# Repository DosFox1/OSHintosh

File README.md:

# OSHintosh
OSHintosh - an open source hardware Diskless 68000 Macintosh with a Bootable ROM Disk, using absolutely no hardware from Apple!

# DISCLAIMER
The initial VDEV1 board required a large amount of bodges to become operational, these are as follows:

1) Added missing track between pin 1 of the 74ls161s, and pin 8 of the 74ls04 inverter
2) 1x missing 47R resistor TSEN2 from pin 11 of the TSG and ASG to ground
3) 4x missing 2k2 pull up resistors on address lines A9, A10, A11, A12
4) 2x missing 3k3 pull up resistors on !AS and !VIAIRQ
5) pin 4 of IC43 should be connected to -12v, not GND
6) pin 12 of IC18 should be connected to track VA11, not track VA12
7) pin 8 of IC43 should be connected to +12v, not 5V
8) errors on silkscreen for R68, R69, R70 and R71 (Schematic and BOM correct, silkscreen incorrect)
9) errors on silkscreen for R40 and R43 (Schematic and BOM correct, silkscreen incorrect)

VDEV2 has been completed and uploaded. This version should fix all problems with the VDEV1 board, but has not been tested. 

# Renders of the VDEV2 Board

# So, what is it?
In a nutshell, the OSHintosh is a Macintosh 512Ke Logic Board - but with the exception that it boots from a disk baked into the ROM, power it provided by an ATX power supply, there is an integrated Pico Scan Converter, as well as a SCHWIM to replace the IWM.
The ROM disk is based off the excellent original (ROMinator)[https://www.bigmessowires.com/mac-rom-inator/], and the OSHintosh also has the option to access further files from a LocalTalk server. 

There is no SCSI, No Floppy Drive or any other Mass Storage - it is effectively a Diskless Workstation!
It could be considered to be the spiritual sucessor to the Macintosh XO (also known as the Macintosh Classic!)

The board has also been designed in only two layers, which reduces the cost of the board even further.
JLCPCB suggest that five boards will cost £30 - so only £6 per board. Your mileage may vary. 
41256 RAM was chosen, as it at least avoids the issue of trying to source 30 pin RAM sockets - which are weirdly expensive now. 
It also makes the entire thing a DIP THT Macintosh!

This makes it the first Macintosh designed on a two layer PCB since the "SCC Word Wide" Prototype from 1982!
The board is more or less ATX shaped, but I didn't place the mounting holes to be ATX compliant. Sorry!

This is intended to fit somewhere between the excellent ITX Plus by Max1zzz and the equally excellent PicoMac by evansm7.  
I say this as the RAM is limited to 512K and there is no mass storage, but it does have "real" Localtalk ports to communicate with an AppleTalk network - as well as sound!

# Programmer Requirements:
A Ti866 or similar programmer is recommended. 
In total there are nine programmable ICs that need to be programmed. These are:
1) 6 x 16V8 GALs
2) 2 x 39F040 EEPROMs
3) 1 x ATTINY85 (RTC)

# Hard (ish) to Source Components:
Please Note that the following ICs may be difficult to source:
1) 15.6672mhz oscillator (ebay may have some, if not, custom oscillators can be ordered)
2) Zilog Z8530 SCC
3) 6522 VIA (Demik has noted that the W65C22N6TPG should be a suitable VIA, that's still being made!)
4) 41256 DRAM (x16!)

Please also note this assumes that you have access to either original Macintosh Peripherals, or will add your own adapters!
The OSHintosh uses the original quadrature 9 pin mouse, as well as the original RJ Keyboard. 

# GAL JED Files:
The GALs were sourced from the PLD archive:
https://wiki.pldarchive.co.uk/index.php?title=Macintosh_128k/512k/Plus
For completeness, they have been included here under "OSHintosh GALs". 

Programming can be completed under minipro with:
```
minipro -p GAL16V8* -w (GAL)16V8.jed
```

Equations will be uploaded... eventually.

# Programming the Attiny85 with Minipro 

The ATTINY85 RTC firmware as developed by pgreenland (https://github.com/pgreenland/attinyrtc) can be programmed with a Ti866 under Minipro:
The following erases the ATTINY85:
```
minipro -p ATTINY85@DIP8 -E
```
Then, the fuses as defined by the file attiny_RTC.fuses is flashed
```
minipro -p ATTINY85@DIP8 -c config -w attiny_RTC.fuses -e
```
Finally, the firmware is flashed to the ATTINY:
```
minipro -p ATTINY85@DIP8 -e -c code -f ihex -w ATtinyRTC.hex
```

# Producing new Rominator Disks with a Minipro 

Normally, the ROMinator is designed to be programmed using the BMOW flasher tool onboard the macintosh.
However, this assumes we already have a method of adding mass storage to the Macintosh, which the OSHintosh lacks. 
(https://www.bigmessowires.com/mac-rom-inator/)

As it transpires, the ROMinator just literally tacks an 885K .DSK image onto the end of the modified ROM.
Therefore, the best way to produce a modded ROM is to use mini vmac (or any other suitable emulator!) to modify a copy of the dsk image 
"rominator-disk.dsk" with the desired files and programs
. I would suggest just deleting any unwanted files rather than erasing the disk, as I feel it might break something if it is erased. 
Once content with the resulting disk, the "raw" rominator binary (basically the rominator rom without the disk image) and the new disk should be concatenated together. 

On a Unix machine, this can be done with cat:
```
cat ROMINATOR_RAW.bin oshintosh_disk.dsk > OSHINTOSH_COMBINED.bin
```

In this example, I am using my oshintosh_disk.dsk to create OSHINTOSH_COMBINED.bin.

The next step is to split the comnbined .bin file into two high and low images for the OSHintosh. 
To generate the HIGH ROM:
```
srec_cat -o HIGH.bin -binary OSHINTOSH_COMBINED.bin -binary -split 2 0
```

To generate the LOW ROM:
```
srec_cat -o LOW.bin -binary OSHINTOSH_COMBINED.bin -binary -split 2 1
```

Finally, the two resulting images can then be flashed to the EEPROMs:
```
minipro -p SST39SF040 -w OSHINTOSH_LOW.bin 
```
```
minipro -p SST39SF040 -w OSHINTOSH_HIGH.bin
```

If successful, the OSHintosh should "ping" rather than the usual chime, and when "R" is pressed, the OSHintosh should boot from the ROM.

# Note regarding AppleShare, Chooser and the OSHintosh Serial Ports

If you are wishing to use appleshare to run programs on the OSHintosh, it is best that you use the OSHintosh Disk.dsk files as a starting point. 

This is as the variant of chooser on this startup disk has been recovered from the Macintosh Classic ROM Disk.

Normally, Chooser does not start up on a locked disk. However, the variant of chooser that is found on the Macintosh Classic ROM Disk does work on locked startup disks!

As such, start with the system file as found in OSHintosh Disk.dsk, or OSHintosh Disk 6.0.8.dsk

Additionally, the printer port/Appleshare is connector CN3 (middle connector), and the Modem connector is CN2 (leftmost connector). 

# Acknowledgements:
Many thanks to:
AlextheCat,
Bitsavers,
Bolle,
Daniel Kottke,
Demik,
GuruThree, 
HKZ,
Mattmos,
Max1zzz,
Pgreenland,
The PLD Archive,

and many others!

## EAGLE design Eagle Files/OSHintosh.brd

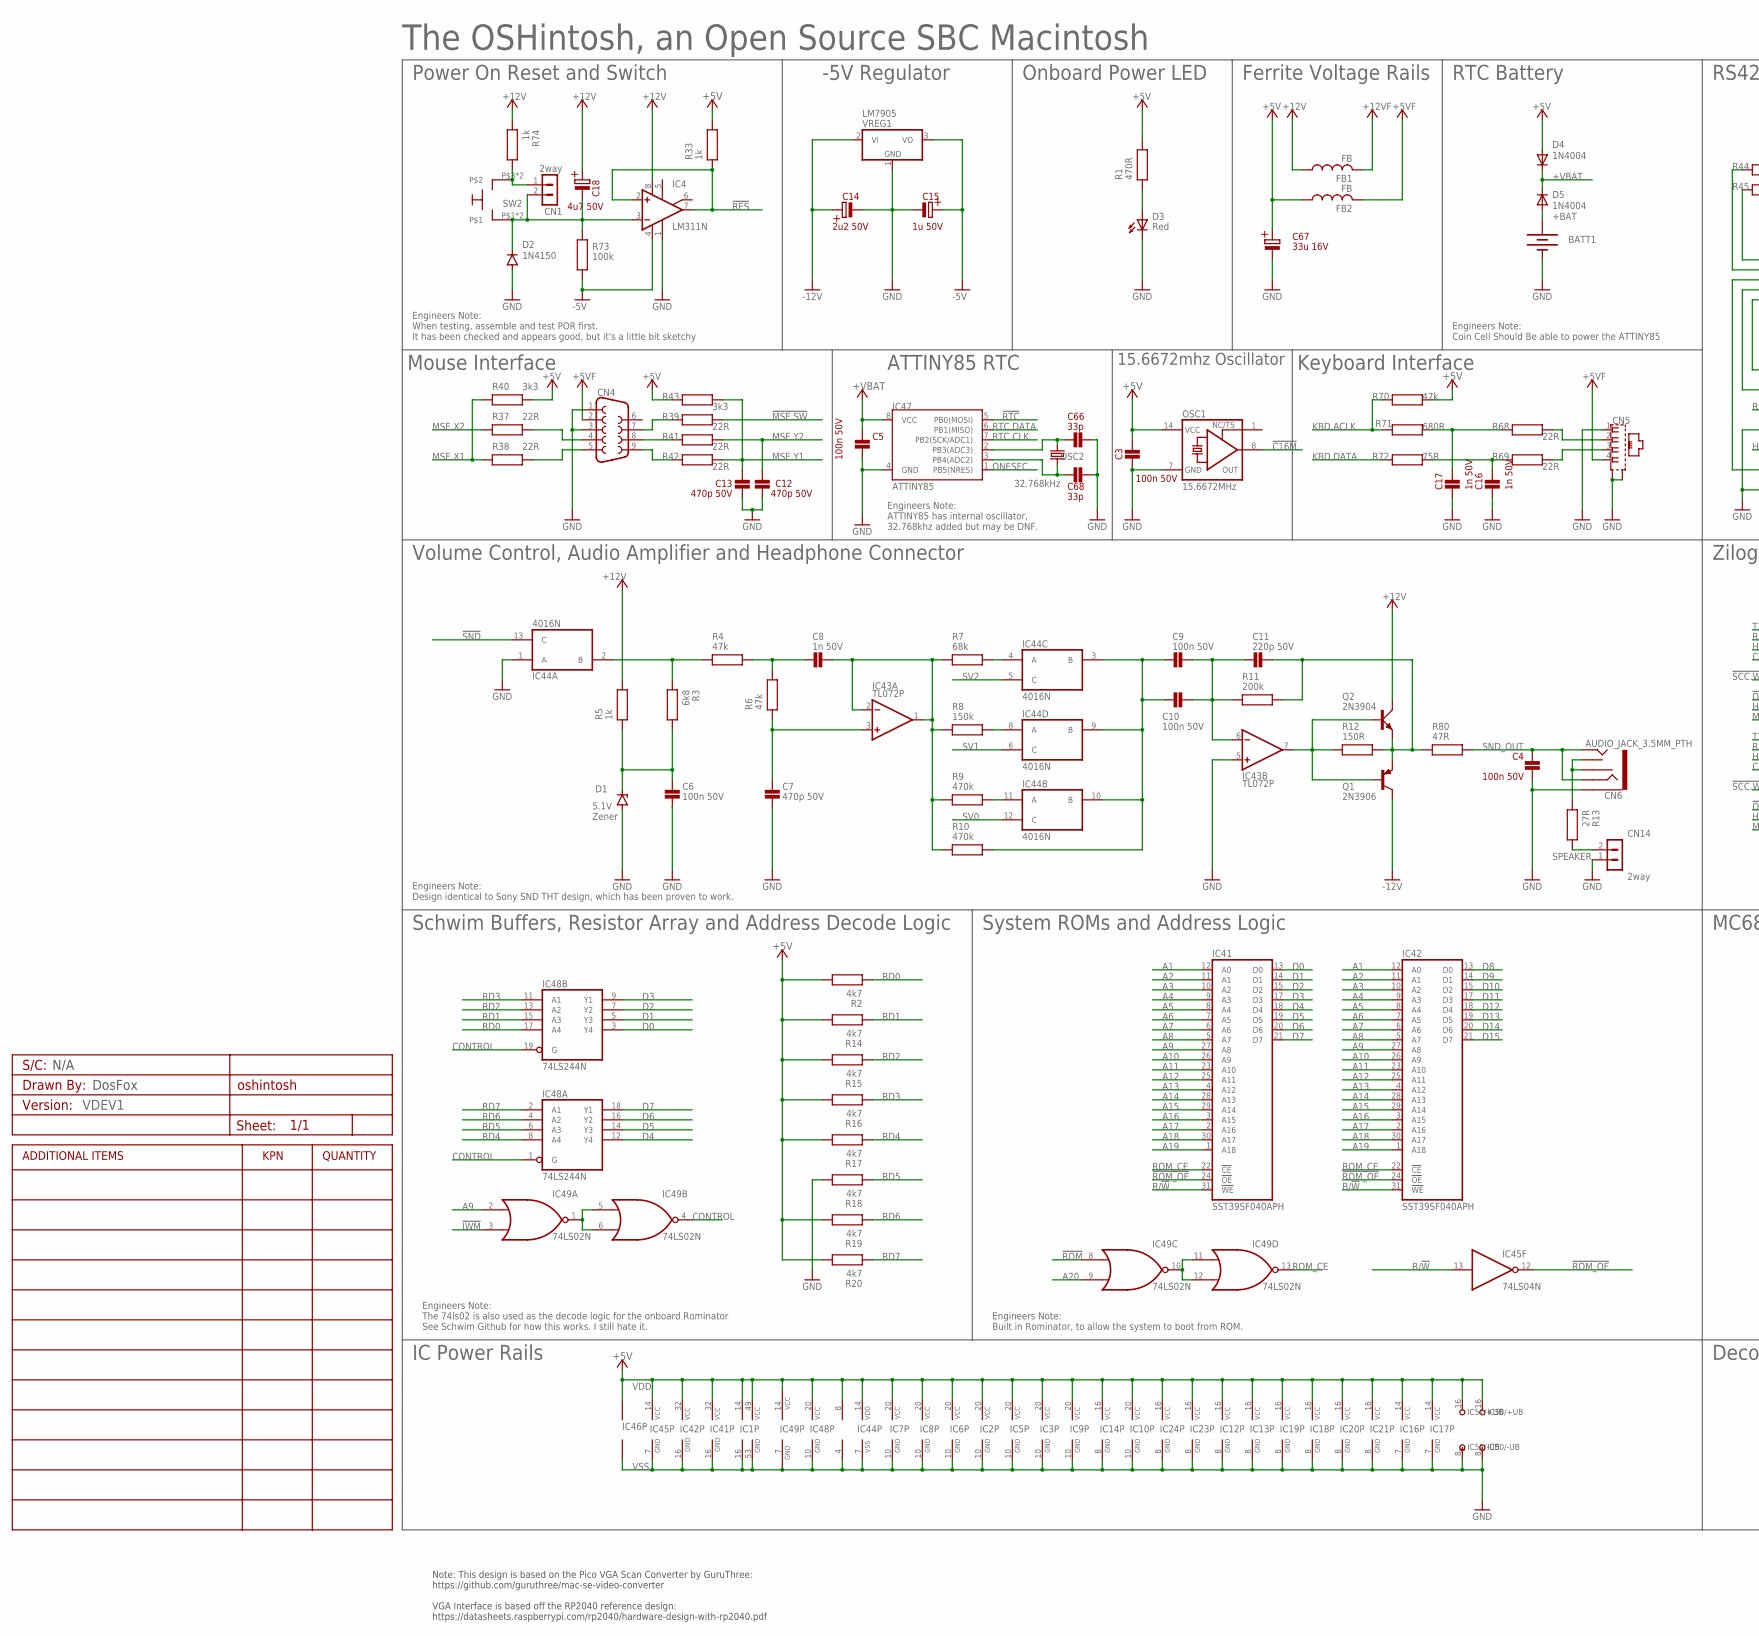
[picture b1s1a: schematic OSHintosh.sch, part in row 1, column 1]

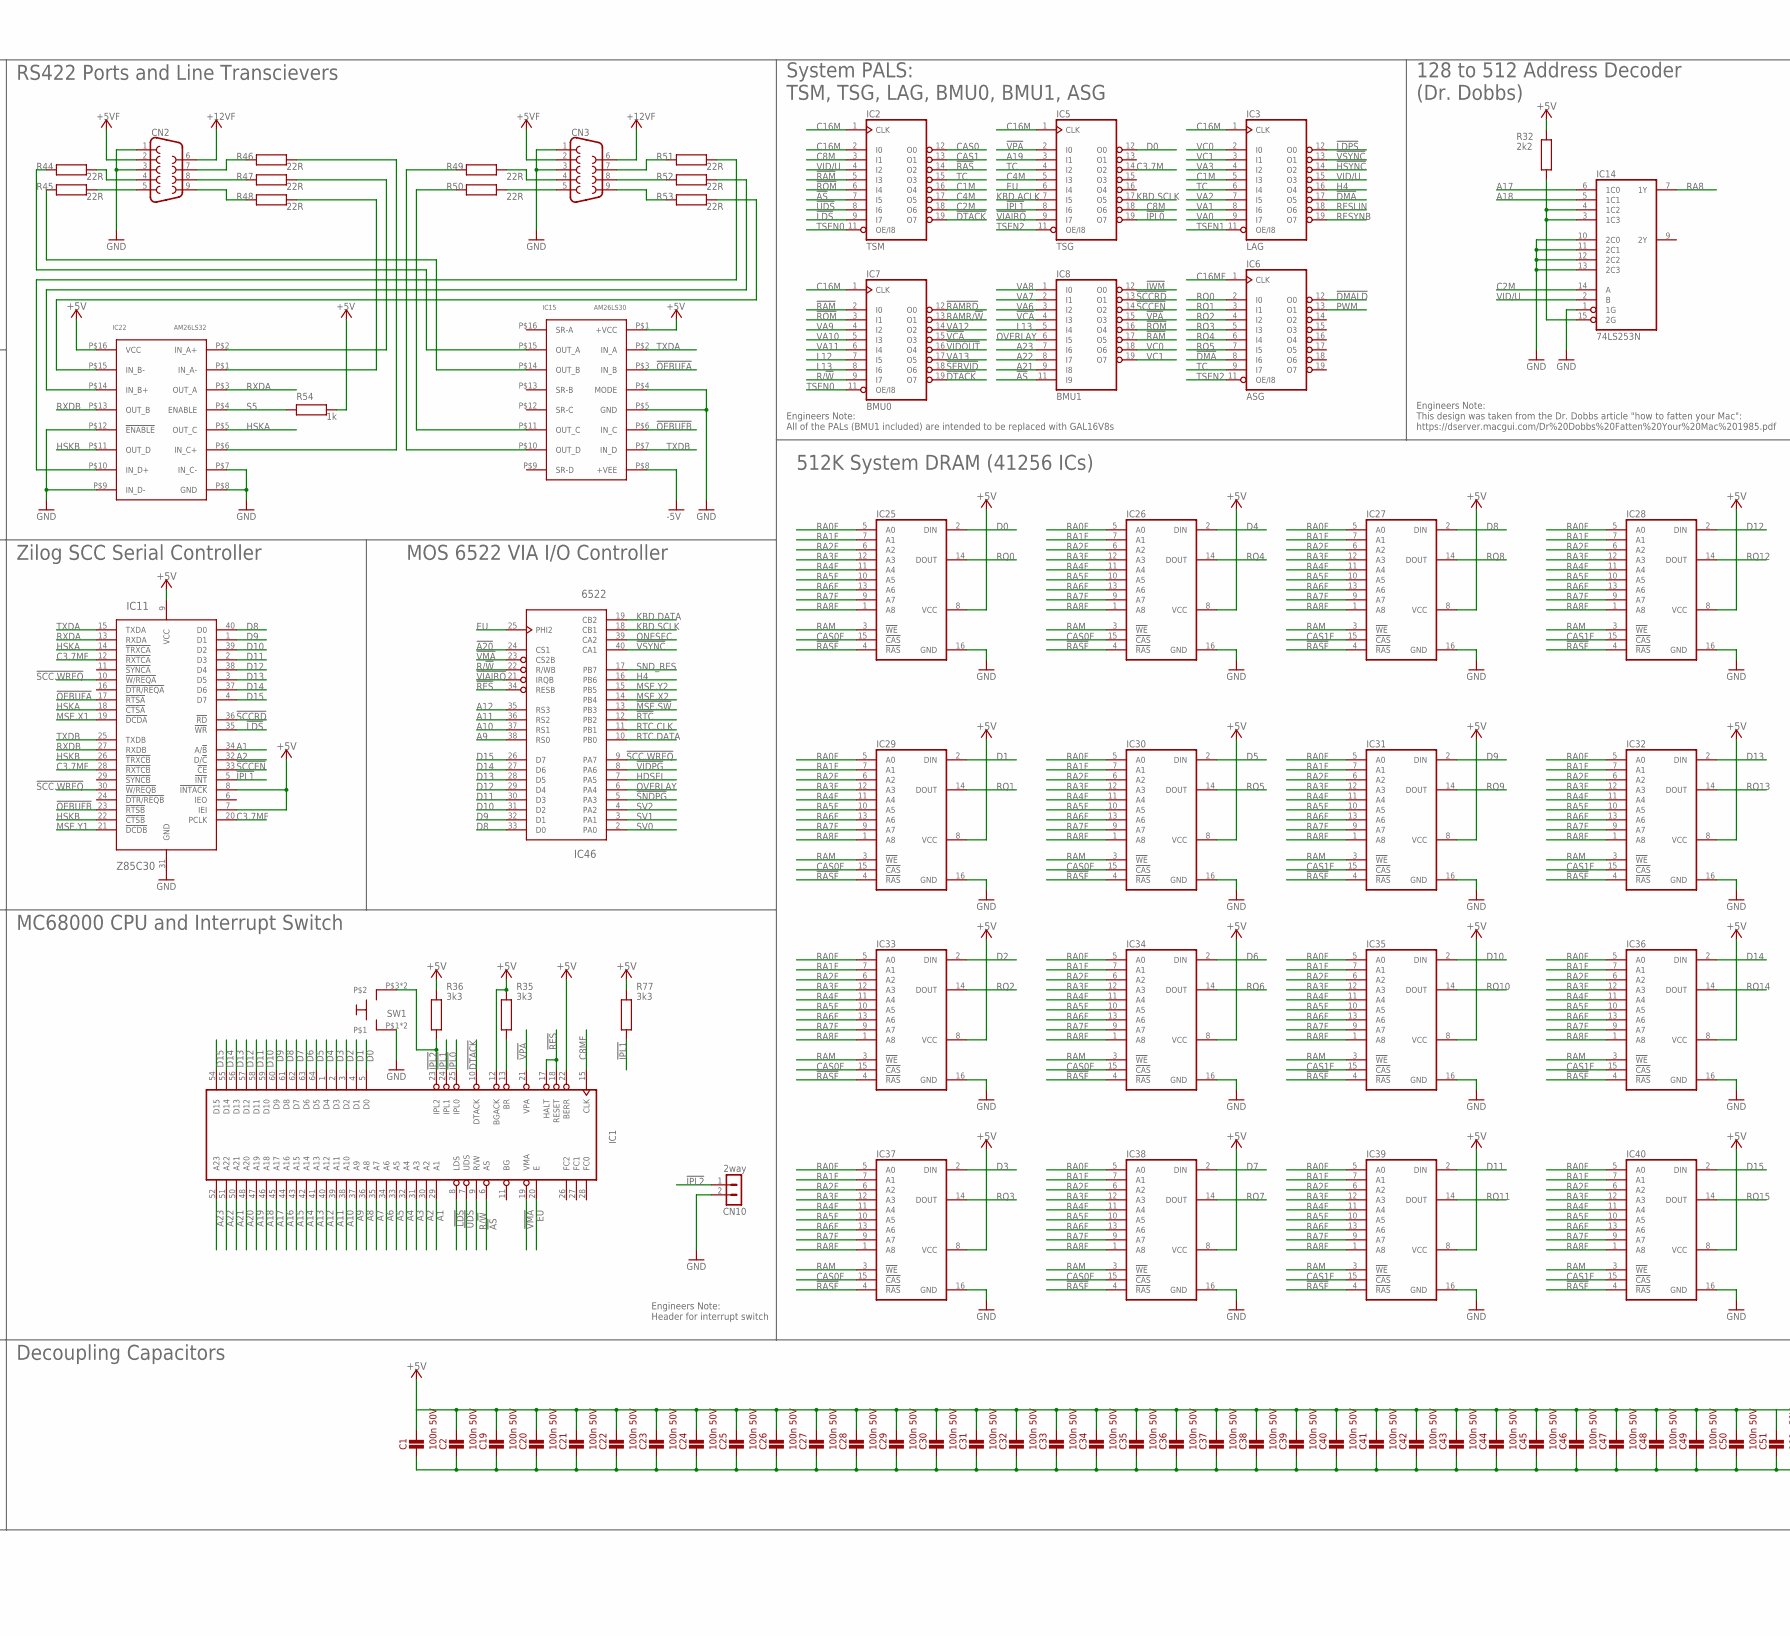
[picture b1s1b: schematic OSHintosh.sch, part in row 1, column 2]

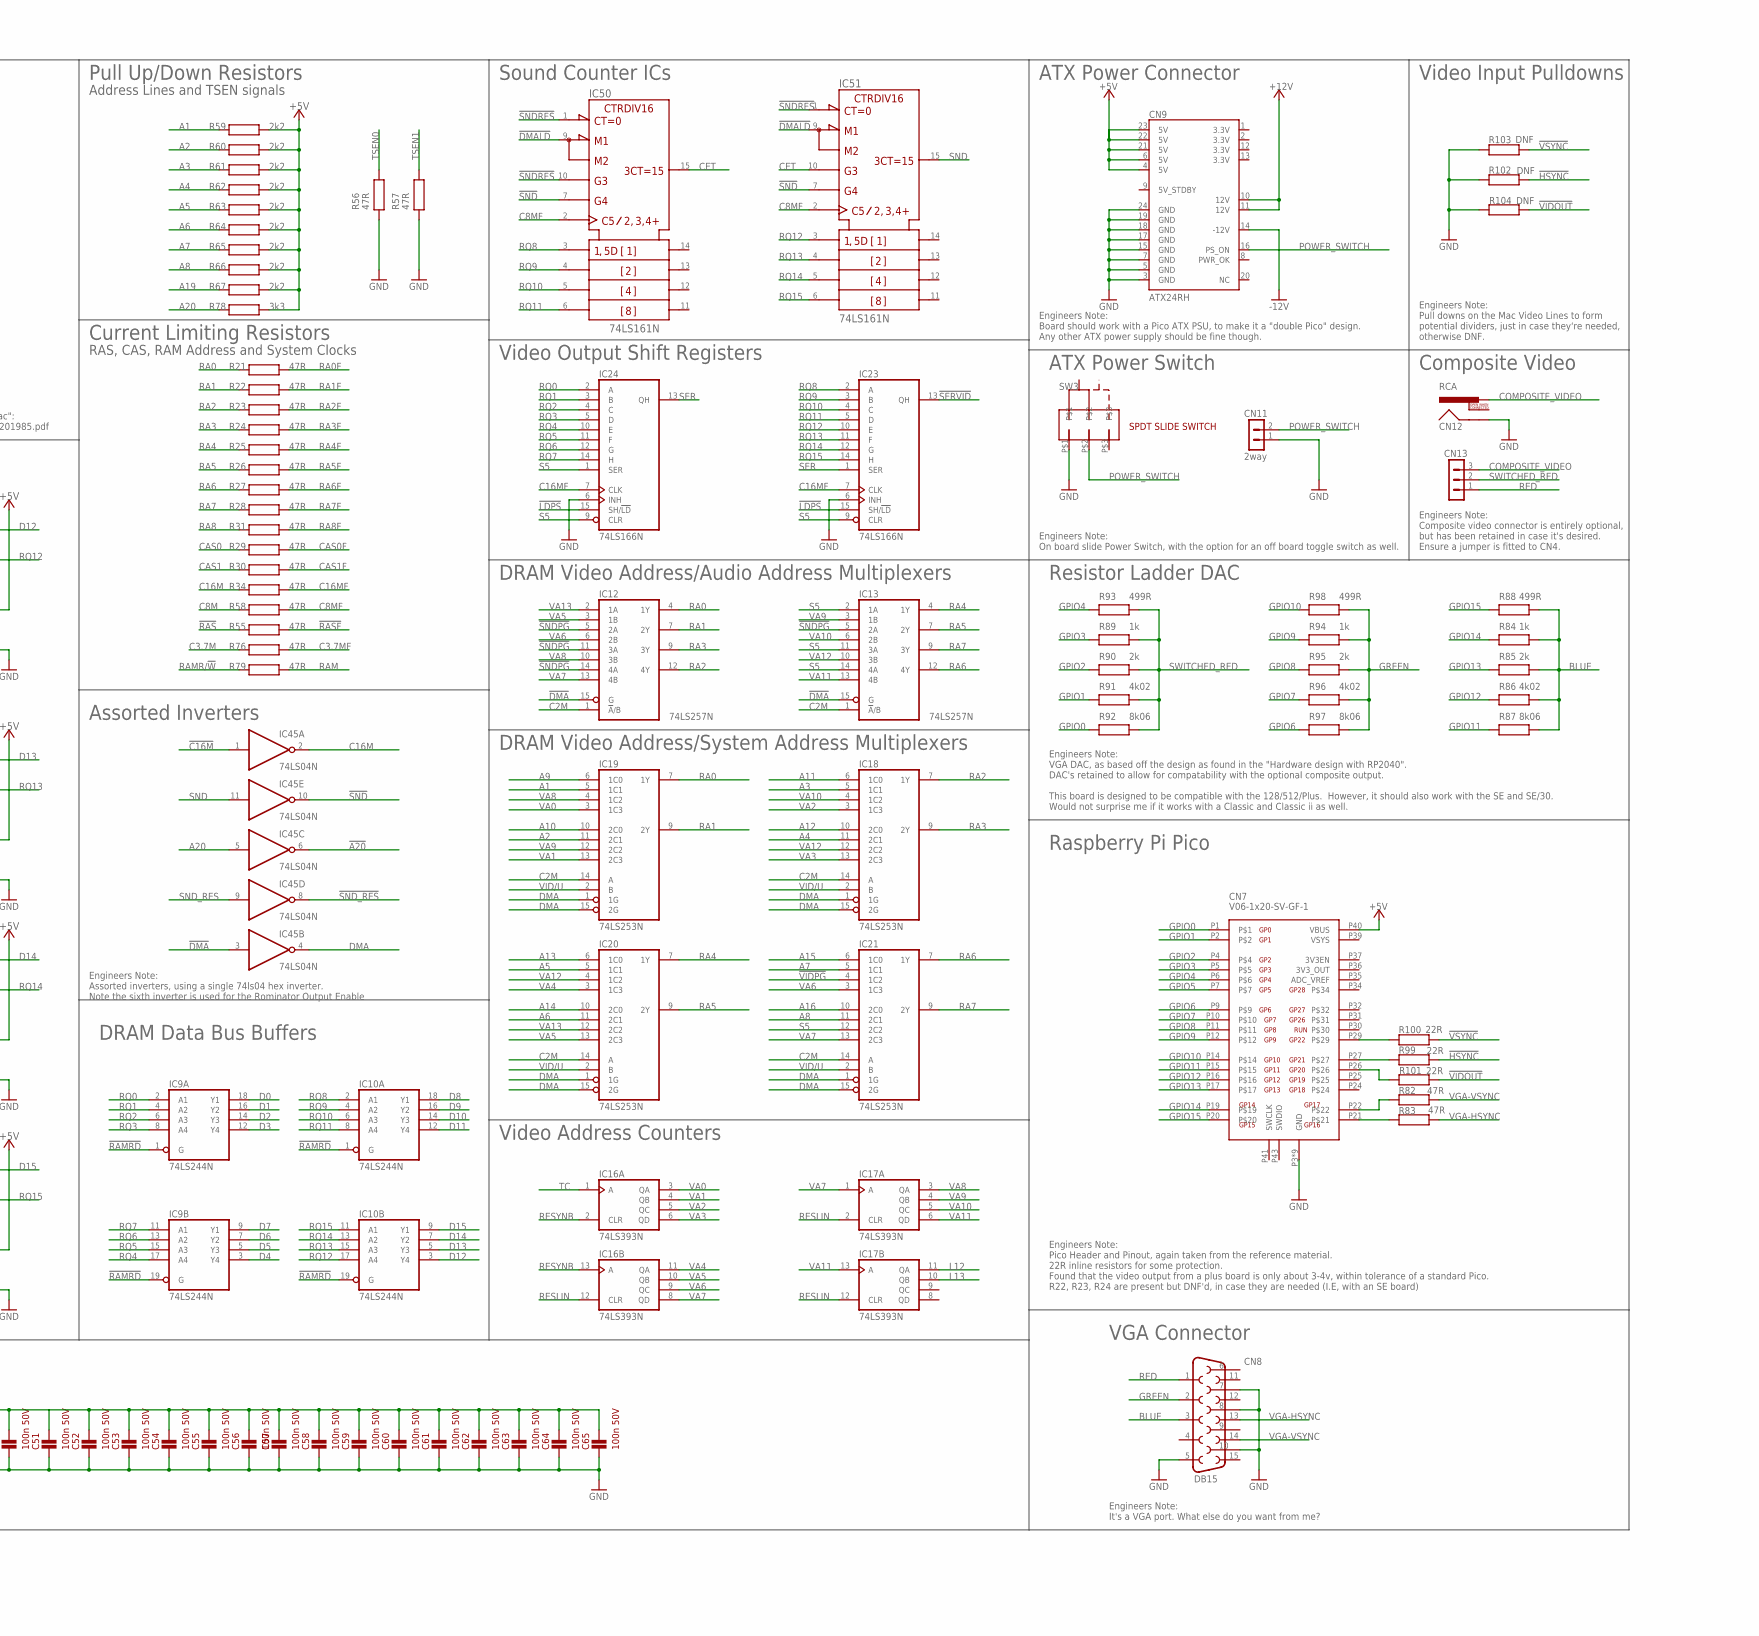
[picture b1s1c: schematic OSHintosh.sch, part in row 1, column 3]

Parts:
A1: VDEV1; PCB_CUSTOM_DETAILS
BATT1: BATTERY-20MM_PTH; BATTCOM_20MM_PTH
C1, C2, C3, C4, C5, C6, C9, C10, C19, C20, C21, C22, C23, C24, C25, C26, C27, C28, C29, C30, C31, C32, C33, C34, C35, C36, C37, C38, C39, C40, C41, C42, C43, C44, C45, C46, C47, C48, C49, C50, C51, C52, C53, C54, C55, C56, C57, C58, C59, C60, C61, C62, C63, C64, C65: 100n 50V; CAP_5.08MM_PITCH
C7, C12, C13: 470p 50V; CAP_5.08MM_PITCH
C8, C16, C17: 1n 50V; CAP_5.08MM_PITCH
C11: 220p 50V; CAP_5.08MM_PITCH
C14: 2u2 50V; CAP_ELECTROLYTIC
C15: 1u 50V; CAP_ELECTROLYTIC
C18: 4u7 50V; CAP_ELECTROLYTIC
C66, C68: 33p; CAP_5.08MM_PITCH
C67: 33u 16V; CAP_ELECTROLYTIC
CN1, CN10, CN11, CN14: 2way; 2W_2.54MM_PITCH_VERT_TH
CN2, CN3, CN4: DB9FEMALE; DB9
CN5: XRJK-S-01-6-4-0-9M2
CN6: AUDIO_JACK_3.5MM_PTH; AUDIO-JACK
CN7: V06-1x20-SV-GF-1; PICO_SOCKET
CN8: DB15
CN9: ATX24RH; ATX24_RIGHT_ANGLE
CN12: RCA
CN13: V06-1x3-SV-GF-1; 3W_2.54MM_PITCH_VERT_TH
D1: ZENER-DIODEF126-10; F126Z10
D2: 1N4150; DO35-7
D3: Red; 5MM_TH_VERT_STANDARD
D4, D5: 1N4004; DO41-10
FB1, FB2: FB
IC1: MC68000P; DIL64
IC2: TSM; DIL20
IC3: LAG; DIL20
IC4: LM311N; DIL08
IC5: TSG; DIL20
IC6: ASG; DIL20
IC7: BMU0; DIL20
IC8: BMU1; DIL20
IC9, IC10, IC48: 74LS244N; DIL20
IC11: Z85C30; DIP40
IC12, IC13: 74LS257N; DIL16
IC14, IC18, IC19, IC20, IC21: 74LS253N; DIL16
IC15: AM26LS30; DIP16
IC16, IC17: 74LS393N; DIL14
IC22: AM26LS32; DIP16
IC23, IC24: 74LS166N; DIL16
IC25, IC26, IC27, IC28, IC29, IC30, IC31, IC32, IC33, IC34, IC35, IC36, IC37, IC38, IC39, IC40: 41256C/D; DIL16
IC41, IC42: SST39SF040APH; DIL32
IC43: TL072P; DIL08
IC44: 4016N; DIL14
IC45: 74LS04N; DIL14
IC46: 6522; DIP-40
IC47: ATTINY85; DIP08_MCU
IC49: 74LS02N; DIL14
IC50, IC51: 74LS161N; DIL16
OSC1: 15.6672MHz; DIL14S
OSC2: 32.768kHz; CRYSTAL-PTH-2X6-CYL
Q1: 2N3906; TO92
Q2: 2N3904; TO92D
R1: 470R; RESISTORTHRUHOLE
R2, R14, R15, R16, R17, R18, R19, R20: 4k7; RESISTORTHRUHOLE
R3: 6k8; RESISTORTHRUHOLE
R4, R6, R70: 47k; RESISTORTHRUHOLE
R5, R33, R54, R74, R84, R89, R94: 1k; RESISTORTHRUHOLE
R7: 68k; RESISTORTHRUHOLE
R8: 150k; RESISTORTHRUHOLE
R9, R10: 470k; RESISTORTHRUHOLE
R11: 200k; RESISTORTHRUHOLE
R12: 150R; RESISTORTHRUHOLE
R13: 27R; RESISTORTHRUHOLE
R21, R22, R23, R24, R25, R26, R27, R28, R29, R30, R31, R34, R55, R56, R57, R58, R76, R79, R80, R82, R83: 47R; RESISTORTHRUHOLE
R32, R59, R60, R61, R62, R63, R64, R65, R66, R67: 2k2; RESISTORTHRUHOLE
R35, R36, R40, R43, R77, R78: 3k3; RESISTORTHRUHOLE
R37, R38, R39, R41, R42, R44, R45, R46, R47, R48, R49, R50, R51, R52, R53, R68, R69, R99, R100, R101: 22R; RESISTORTHRUHOLE
R71: 680R; RESISTORTHRUHOLE
R72: 75R; RESISTORTHRUHOLE
R73: 100k; RESISTORTHRUHOLE
R85, R90, R95: 2k; RESISTORTHRUHOLE
R86, R91, R96: 4k02; RESISTORTHRUHOLE
R87, R92, R97: 8k06; RESISTORTHRUHOLE
R88, R93, R98: 499R; RESISTORTHRUHOLE
R102, R103, R104: DNF; RESISTORTHRUHOLE
SW1, SW2: DTS-61; DIP_DTS_6_TACT_SWITCH_6X6_TH
SW3: SS12D16-GDN5; THRUHOLE90DEGSLIDESW
VREG1: LM7905; TO220H

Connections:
!A20: IC45.6 (O), IC46.24 (CS1)
!AS: IC1.6 (AS), IC2.7 (I5), IC8.11 (I9)
!C16M: IC45.1 (I), OSC1.8 (OUT)
!DMA: IC3.17 (O5), IC6.8 (I6), IC12.15 (G), IC13.15 (G), IC45.3 (I)
!DMALD: IC6.12 (O0), IC50.9 (!LOAD), IC51.9 (!LOAD)
!DTACK: IC1.10 (DTACK), IC2.19 (O7), IC7.19 (O7)
!HSYNC: IC3.14 (O2), R99.P$2, R102.P$2
!IPL0: IC1.25 (IPL0), IC5.19 (O7)
!IPL1: IC1.24 (IPL1), IC5.8 (I6), IC11.5 (!INT), R77.P$1
!IPL2: CN10.1, IC1.23 (IPL2), R36.P$1, SW1.P$3, SW1.P$4
!IWM: IC8.12 (O0), IC49.3 (I1)
!LDPS: IC3.12 (O0), IC23.15 (SH/!LD), IC24.15 (SH/!LD)
!LDS: IC1.8 (LDS), IC2.9 (I7), IC11.35 (!WR)
!MSE.SW: IC46.13 (PB3), R39.P$2
!OEBUFA: IC11.17 (!RTSA), IC15.P$3 (IN_B)
!OEBUFB: IC11.23 (!RTSB), IC15.P$6 (IN_C)
!RAM: IC2.5 (I3), IC7.2 (I0), IC8.17 (O5)
!RAMRD: IC7.12 (O0), IC9.1 (G), IC9.19 (G), IC10.1 (G), IC10.19 (G)
!RAS: IC2.14 (O2), R55.P$1
!RASF: IC25.4 (!RAS), IC26.4 (!RAS), IC27.4 (!RAS), IC28.4 (!RAS), IC29.4 (!RAS), IC30.4 (!RAS), IC31.4 (!RAS), IC32.4 (!RAS), IC33.4 (!RAS), IC34.4 (!RAS), IC35.4 (!RAS), IC36.4 (!RAS), IC37.4 (!RAS), IC38.4 (!RAS), IC39.4 (!RAS), IC40.4 (!RAS), R55.P$2
!RES: IC1.17 (HALT), IC1.18 (RESET), IC4.2 (+IN), IC4.7 (OUT), IC46.34 (RESB), R33.P$1
!ROM: IC2.6 (I4), IC7.3 (I1), IC8.16 (O4), IC49.8 (I0)
!ROM_OE: IC41.24 (!OE), IC42.24 (!OE), IC45.12 (O)
!RTC: IC46.12 (PB2), IC47.5 (PB0(MOSI))
!SCC.WREQ: IC11.10 (!W/REQA), IC11.30 (!W/REQB), IC46.9 (PA7)
!SCCEN: IC8.14 (O2), IC11.33 (!CE)
!SCCRD: IC8.13 (O1), IC11.36 (!RD)
!SERVID: IC7.18 (O6), IC23.13 (QH)
!SND: IC44.13 (C), IC45.10 (O), IC50.7 (ENP), IC51.7 (ENP)
!SNDPG: IC12.5 (2A), IC12.11 (3A), IC12.14 (4A), IC13.5 (2A), IC46.5 (PA3)
!SNDRES: IC50.1 (!CLR), IC50.10 (ENT), IC51.1 (!CLR)
!SND_RES: IC45.8 (O)
!UDS: IC1.7 (UDS), IC2.8 (I6)
!VCA: IC7.15 (O3), IC8.4 (I3)
!VIAIRQ: IC5.9 (I7), IC46.21 (IRQB)
!VIDOUT: IC7.16 (O4), R101.P$2, R104.P$2
!VIDPG: IC21.4 (1C2), IC46.8 (PA6)
!VMA: IC1.19 (VMA), IC46.23 (CS2B)
!VPA: IC1.21 (VPA), IC5.2 (I0), IC8.15 (O3)
!VSYNC: IC3.13 (O1), IC46.40 (CA1), R100.P$2, R103.P$2
+5V: C1.P$2, C2.P$2, C3.P$2, C19.P$2, C20.P$2, C21.P$2, C22.P$2, C23.P$2, C24.P$2, C25.P$2, C26.P$2, C27.P$2, C28.P$2, C29.P$2, C30.P$2, C31.P$2, C32.P$2, C33.P$2, C34.P$2, C35.P$2, C36.P$2, C37.P$2, C38.P$2, C39.P$2, C40.P$2, C41.P$2, C42.P$2, C43.P$2, C44.P$2, C45.P$2, C46.P$2, C47.P$2, C48.P$2, C49.P$2, C50.P$2, C51.P$2, C52.P$2, C53.P$2, C54.P$2, C55.P$2, C56.P$2, C57.P$2, C58.P$2, C59.P$2, C60.P$2, C61.P$2, C62.P$2, C63.P$2, C64.P$2, C65.P$2, C67.P$1, CN7.P40 (VBUS), CN9.4 (5V), CN9.6 (5V), CN9.21 (5V), CN9.22 (5V), CN9.23 (5V), D4.A, FB2.P$1 (1), IC1.12 (BGACK), IC1.14 (VCC), IC1.22 (BERR), IC1.49 (VCC), IC2.20 (VCC), IC3.20 (VCC), IC5.20 (VCC), IC6.20 (VCC), IC7.20 (VCC), IC8.20 (VCC), IC9.20 (VCC), IC10.20 (VCC), IC11.7 (IEI), IC11.8 (!INTACK), IC11.9 (VCC), IC12.16 (VCC), IC13.16 (VCC), IC14.16 (VCC), IC15.P$1 (+VCC), IC16.14 (VCC), IC17.14 (VCC), IC18.16 (VCC), IC19.16 (VCC), IC20.16 (VCC), IC21.16 (VCC), IC22.P$16 (VCC), IC23.16 (VCC), IC24.16 (VCC), IC25.8 (VCC), IC26.8 (VCC), IC27.8 (VCC), IC28.8 (VCC), IC29.8 (VCC), IC30.8 (VCC), IC31.8 (VCC)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
+5VF: CN2.2, CN3.2, CN4.2, CN5.4, FB2.P$2 (2)
+12V: C18.P$1, CN9.10 (12V), CN9.11 (12V), FB1.P$1 (1), IC4.8 (V+), Q2.C, R5.P$2, R74.P$1
+12VF: CN2.6, CN3.6, FB1.P$2 (2)
+BAT: BATT1.1 (+), D5.A
+VBAT: C5.P$2, D4.C, D5.C, IC47.8 (VCC)
-5V: C15.P$1, IC4.4 (V-), IC15.P$8 (+VEE), R73.P$1, VREG1.3 (VO)
-12V: C14.P$1, CN9.14 (-12V), Q1.1 (C), VREG1.2 (VI)
A1: IC1.29 (A1), IC11.34 (A/!B), IC19.5 (1C1), IC41.12 (A0), IC42.12 (A0), R59.P$1
A2: IC1.30 (A2), IC11.32 (D/!C), IC19.11 (2C1), IC41.11 (A1), IC42.11 (A1), R60.P$1
A3: IC1.31 (A3), IC18.5 (1C1), IC41.10 (A2), IC42.10 (A2), R61.P$1
A4: IC1.32 (A4), IC18.11 (2C1), IC41.9 (A3), IC42.9 (A3), R62.P$1
A5: IC1.33 (A5), IC20.5 (1C1), IC41.8 (A4), IC42.8 (A4), R63.P$1
A6: IC1.34 (A6), IC20.11 (2C1), IC41.7 (A5), IC42.7 (A5), R64.P$1
A7: IC1.35 (A7), IC21.5 (1C1), IC41.6 (A6), IC42.6 (A6), R65.P$1
A8: IC1.36 (A8), IC21.11 (2C1), IC41.5 (A7), IC42.5 (A7), R66.P$1
A9: IC1.37 (A9), IC19.6 (1C0), IC41.27 (A8), IC42.27 (A8), IC46.38 (RS0), IC49.2 (I0)
A10: IC1.38 (A10), IC19.10 (2C0), IC41.26 (A9), IC42.26 (A9), IC46.37 (RS1)
A11: IC1.39 (A11), IC18.6 (1C0), IC41.23 (A10), IC42.23 (A10), IC46.36 (RS2)
A12: IC1.40 (A12), IC18.10 (2C0), IC41.25 (A11), IC42.25 (A11), IC46.35 (RS3)
A13: IC1.41 (A13), IC20.6 (1C0), IC41.4 (A12), IC42.4 (A12)
A14: IC1.42 (A14), IC20.10 (2C0), IC41.28 (A13), IC42.28 (A13)
A15: IC1.43 (A15), IC21.6 (1C0), IC41.29 (A14), IC42.29 (A14)
A16: IC1.44 (A16), IC21.10 (2C0), IC41.3 (A15), IC42.3 (A15)
A17: IC1.45 (A17), IC14.6 (1C0), IC41.2 (A16), IC42.2 (A16)
A18: IC1.46 (A18), IC14.5 (1C1), IC41.30 (A17), IC42.30 (A17)
A19: IC1.47 (A19), IC5.3 (I1), IC41.1 (A18), IC42.1 (A18), R67.P$1
A20: IC1.48 (A20), IC45.5 (I), IC49.9 (I1), R78.P$1
A21: IC1.50 (A21), IC8.9 (I8)
A22: IC1.51 (A22), IC8.8 (I7)
A23: IC1.52 (A23), IC8.7 (I6)
BLUE: CN8.3, R84.P$2, R85.P$2, R86.P$2, R87.P$2, R88.P$2
C1M: IC2.16 (O4), IC3.5 (I3)
C2M: IC2.18 (O6), IC12.1 (!A!/B), IC13.1 (!A!/B), IC14.14 (A), IC18.14 (A), IC19.14 (A), IC20.14 (A), IC21.14 (A)
C3.7M: IC5.14 (O2), R76.P$1
C3.7MF: IC11.12 (!RXTCA), IC11.20 (PCLK), IC11.28 (!RXTCB), R76.P$2
C4M: IC2.17 (O5), IC5.5 (I3)
C8M: IC2.3 (I1), IC5.18 (O6), R58.P$1
C8MF: IC1.15 (CLK), IC50.2 (CLK), IC51.2 (CLK), R58.P$2
C16M: IC2.1 (CLK), IC2.2 (I0), IC3.1 (CLK), IC5.1 (CLK), IC7.1 (CLK), IC45.2 (O), R34.P$1
C16MF: IC6.1 (CLK), IC23.7 (CLK), IC24.7 (CLK), R34.P$2
CAS0: IC2.12 (O0), R29.P$1
CAS0F: IC25.15 (!CAS), IC26.15 (!CAS), IC29.15 (!CAS), IC30.15 (!CAS), IC33.15 (!CAS), IC34.15 (!CAS), IC37.15 (!CAS), IC38.15 (!CAS), R29.P$2
CAS1: IC2.13 (O1), R30.P$1
CAS1F: IC27.15 (!CAS), IC28.15 (!CAS), IC31.15 (!CAS), IC32.15 (!CAS), IC35.15 (!CAS), IC36.15 (!CAS), IC39.15 (!CAS), IC40.15 (!CAS), R30.P$2
CET: IC50.15 (RCO), IC51.10 (ENT)
COMPOSITE_VIDEO: CN12.PIN, CN13.3
CONTROL: IC48.1 (G), IC48.19 (G), IC49.4 (O)
D0: IC1.5 (D0), IC5.12 (O0), IC9.18 (Y1), IC25.2 (DIN), IC41.13 (D0), IC48.3 (Y4)
D1: IC1.4 (D1), IC9.16 (Y2), IC29.2 (DIN), IC41.14 (D1), IC48.5 (Y3)
D2: IC1.3 (D2), IC9.14 (Y3), IC33.2 (DIN), IC41.15 (D2), IC48.7 (Y2)
D3: IC1.2 (D3), IC9.12 (Y4), IC37.2 (DIN), IC41.17 (D3), IC48.9 (Y1)
D4: IC1.1 (D4), IC9.3 (Y4), IC26.2 (DIN), IC41.18 (D4), IC48.12 (Y4)
D5: IC1.64 (D5), IC9.5 (Y3), IC30.2 (DIN), IC41.19 (D5), IC48.14 (Y3)
D6: IC1.63 (D6), IC9.7 (Y2), IC34.2 (DIN), IC41.20 (D6), IC48.16 (Y2)
D7: IC1.62 (D7), IC9.9 (Y1), IC38.2 (DIN), IC41.21 (D7), IC48.18 (Y1)
D8: IC1.61 (D8), IC10.18 (Y1), IC11.40 (D0), IC27.2 (DIN), IC42.13 (D0), IC46.33 (D0)
D9: IC1.60 (D9), IC10.16 (Y2), IC11.1 (D1), IC31.2 (DIN), IC42.14 (D1), IC46.32 (D1)
D10: IC1.59 (D10), IC10.14 (Y3), IC11.39 (D2), IC35.2 (DIN), IC42.15 (D2), IC46.31 (D2)
D11: IC1.58 (D11), IC10.12 (Y4), IC11.2 (D3), IC39.2 (DIN), IC42.17 (D3), IC46.30 (D3)
D12: IC1.57 (D12), IC10.3 (Y4), IC11.38 (D4), IC28.2 (DIN), IC42.18 (D4), IC46.29 (D4)
D13: IC1.56 (D13), IC10.5 (Y3), IC11.3 (D5), IC32.2 (DIN), IC42.19 (D5), IC46.28 (D5)
D14: IC1.55 (D14), IC10.7 (Y2), IC11.37 (D6), IC36.2 (DIN), IC42.20 (D6), IC46.27 (D6)
D15: IC1.54 (D15), IC10.9 (Y1), IC11.4 (D7), IC40.2 (DIN), IC42.21 (D7), IC46.26 (D7)
DMA: IC18.1 (1G), IC18.15 (2G), IC19.1 (1G), IC19.15 (2G), IC20.1 (1G), IC20.15 (2G), IC21.1 (1G), IC21.15 (2G), IC45.4 (O)
EU: IC1.20 (E), IC5.6 (I4), IC46.25 (PHI2)
GND: BATT1.2 (-), C1.P$1, C2.P$1, C3.P$1, C4.P$2, C5.P$1, C6.P$1, C7.P$1, C12.P$1, C13.P$1, C14.P$2, C15.P$2, C16.P$1, C17.P$1, C19.P$1, C20.P$1, C21.P$1, C22.P$1, C23.P$1, C24.P$1, C25.P$1, C26.P$1, C27.P$1, C28.P$1, C29.P$1, C30.P$1, C31.P$1, C32.P$1, C33.P$1, C34.P$1, C35.P$1, C36.P$1, C37.P$1, C38.P$1, C39.P$1, C40.P$1, C41.P$1, C42.P$1, C43.P$1, C44.P$1, C45.P$1, C46.P$1, C47.P$1, C48.P$1, C49.P$1, C50.P$1, C51.P$1, C52.P$1, C53.P$1, C54.P$1, C55.P$1, C56.P$1, C57.P$1, C58.P$1, C59.P$1, C60.P$1, C61.P$1, C62.P$1, C63.P$1, C64.P$1, C65.P$1, C66.P$2, C67.P$2, C68.P$2, CN2.1, CN2.3, CN3.1, CN3.3, CN4.1, CN4.3, CN5.1, CN5.S1 (S), CN5.S2 (S), CN6.SLEEVE, CN7.P3 (GND), CN7.P8 (GND), CN7.P13 (GND), CN7.P18 (GND), CN7.P23 (GND), CN7.P28 (GND), CN7.P33 (GND), CN7.P38 (GND), CN7.P42 (GND), CN8.5, CN8.7, CN8.8, CN8.10, CN9.3 (GND), CN9.5 (GND), CN9.7 (GND), CN9.15 (GND), CN9.17 (GND), CN9.18 (GND), CN9.19 (GND)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
GPIO0: CN7.P1, R92.P$1
GPIO1: CN7.P2, R91.P$1
GPIO2: CN7.P4, R90.P$1
GPIO3: CN7.P5, R89.P$1
GPIO4: CN7.P6, R93.P$1
GPIO5: CN7.P7
GPIO6: CN7.P9, R97.P$1
GPIO7: CN7.P10, R96.P$1
GPIO8: CN7.P11, R95.P$1
GPIO9: CN7.P12, R94.P$1
GPIO10: CN7.P14, R98.P$1
GPIO11: CN7.P15, R87.P$1
GPIO12: CN7.P16, R86.P$1
GPIO13: CN7.P17, R85.P$1
GPIO14: CN7.P19, R84.P$1
GPIO15: CN7.P20, R88.P$1
GREEN: CN8.2, R94.P$2, R95.P$2, R96.P$2, R97.P$2, R98.P$2
H4: IC3.16 (O4), IC46.16 (PB6)
HDSEL: IC46.7 (PA5)
HSKA: IC11.14 (!TRXCA), IC11.18 (!CTSA), IC22.P$5 (OUT_C)
HSKB: IC11.22 (!CTSB), IC11.26 (!TRXCB), IC22.P$11 (OUT_D)
KBD.ACLK: IC5.7 (I5), R70.P$1, R71.P$2
KBD.DATA: IC46.19 (CB2), R72.P$1
KBD.SCLK: IC5.17 (O5), IC46.18 (CB1)
L12: IC7.7 (I5), IC17.11 (QA)
L13: IC7.8 (I6), IC8.5 (I4), IC17.10 (QB)
MSE.X1: IC11.19 (!DCDA), R38.P$1, R40.P$1
MSE.X2: IC46.14 (PB4), R37.P$1
MSE.Y1: C13.P$2, IC11.21 (!DCDB), R42.P$2, R43.P$1
MSE.Y2: C12.P$2, IC46.15 (PB5), R41.P$2
unnamed: D3.A, R1.P$1
unnamed: IC44.2 (B), R3.P$1, R4.P$1
unnamed: C9.P$1, C10.P$1, IC44.3 (B), IC44.9 (B), IC44.10 (B), R10.P$2
unnamed: C8.P$1, R4.P$2, R6.P$2
unnamed: C6.P$2, D1.C, R3.P$2, R5.P$1
unnamed: C7.P$2, IC43.3 (+IN), R6.P$1
unnamed: IC44.4 (A), R7.P$2
unnamed: IC44.8 (A), R8.P$2
unnamed: IC44.11 (A), R9.P$2
unnamed: C9.P$2, C10.P$2, C11.P$1, IC43.6 (-IN), R11.P$1
unnamed: C8.P$2, IC43.1 (OUT), IC43.2 (-IN), R7.P$1, R8.P$1, R9.P$1, R10.P$1
unnamed: C11.P$2, Q1.3 (E), Q2.E, R11.P$2, R12.P$2, R80.P$1
unnamed: IC49.1 (O), IC49.5 (I0), IC49.6 (I1)
unnamed: IC43.7 (OUT), Q1.2 (B), Q2.B, R12.P$1
unnamed: IC49.10 (O), IC49.11 (I0), IC49.12 (I1)
unnamed: IC14.3 (1C3), IC14.4 (1C2), IC14.15 (2G), R32.P$1
unnamed: IC1.13 (BR), R35.P$1
unnamed: CN6.RSH, CN6.TSH, R13.P$1
unnamed: CN4.5, R38.P$2
unnamed: CN4.4, R37.P$2
unnamed: CN4.7, R39.P$1
unnamed: C66.P$1, IC47.2 (PB3(ADC3)), OSC2.2
unnamed: C68.P$1, IC47.3 (PB4(ADC2)), OSC2.1
unnamed: CN4.8, R41.P$1
unnamed: CN4.9, R42.P$1
unnamed: CN5.2, R68.P$2
unnamed: IC15.P$14 (OUT_B), R45.P$1
unnamed: IC22.P$6 (IN_C+), R46.P$2
unnamed: CN2.4, R44.P$2
unnamed: CN2.5, R45.P$2
unnamed: IC22.P$2 (IN_A+), R47.P$2
unnamed: CN2.7, R46.P$1
unnamed: CN2.8, R47.P$1
unnamed: CN2.9, R48.P$1
unnamed: IC22.P$1 (IN_A-), R48.P$2
unnamed: CN3.4, R49.P$2
unnamed: CN3.5, R50.P$2
unnamed: CN3.7, R51.P$1
unnamed: CN3.8, R52.P$1
unnamed: CN3.9, R53.P$1
unnamed: IC15.P$10 (OUT_D), R49.P$1
unnamed: IC15.P$11 (OUT_C), R50.P$1
unnamed: IC22.P$10 (IN_D+), R51.P$2
unnamed: IC22.P$14 (IN_B+), R52.P$2
unnamed: IC22.P$15 (IN_B-), R53.P$2
unnamed: IC15.P$15 (OUT_A), R44.P$1
unnamed: CN5.3, R69.P$2
unnamed: C17.P$2, R68.P$1, R71.P$1
unnamed: C16.P$2, R69.P$1, R72.P$2
unnamed: C18.P$2, CN1.2, D2.C, IC4.3 (-IN), R73.P$2, SW2.P$1, SW2.P$2
unnamed: CN1.1, R74.P$2, SW2.P$3, SW2.P$4
unnamed: CN7.P22, R82.P$1
unnamed: CN7.P21, R83.P$1
unnamed: CN7.P29, R100.P$1
unnamed: CN7.P27, R99.P$1
unnamed: CN7.P26, R101.P$1
ONESEC: IC46.39 (CA2), IC47.1 (PB5(NRES))
OVERLAY: IC8.6 (I5), IC46.6 (PA4)
POWER_SWITCH: CN9.16 (PS_ON), CN11.2, SW3.P$2
PWM: IC6.13 (O1)
R/!W: IC1.9 (R/W), IC7.9 (I7), IC41.31 (!WE), IC42.31 (!WE), IC45.13 (I), IC46.22 (R/WB)
RA0: IC12.4 (1Y), IC19.7 (1Y), R21.P$1
RA0F: IC25.5 (A0), IC26.5 (A0), IC27.5 (A0), IC28.5 (A0), IC29.5 (A0), IC30.5 (A0), IC31.5 (A0), IC32.5 (A0), IC33.5 (A0), IC34.5 (A0), IC35.5 (A0), IC36.5 (A0), IC37.5 (A0), IC38.5 (A0), IC39.5 (A0), IC40.5 (A0), R21.P$2
RA1: IC12.7 (2Y), IC19.9 (2Y), R22.P$1
RA1F: IC25.7 (A1), IC26.7 (A1), IC27.7 (A1), IC28.7 (A1), IC29.7 (A1), IC30.7 (A1), IC31.7 (A1), IC32.7 (A1), IC33.7 (A1), IC34.7 (A1), IC35.7 (A1), IC36.7 (A1), IC37.7 (A1), IC38.7 (A1), IC39.7 (A1), IC40.7 (A1), R22.P$2
RA2: IC12.12 (4Y), IC18.7 (1Y), R23.P$1
RA2F: IC25.6 (A2), IC26.6 (A2), IC27.6 (A2), IC28.6 (A2), IC29.6 (A2), IC30.6 (A2), IC31.6 (A2), IC32.6 (A2), IC33.6 (A2), IC34.6 (A2), IC35.6 (A2), IC36.6 (A2), IC37.6 (A2), IC38.6 (A2), IC39.6 (A2), IC40.6 (A2), R23.P$2
RA3: IC12.9 (3Y), IC18.9 (2Y), R24.P$1
RA3F: IC25.12 (A3), IC26.12 (A3), IC27.12 (A3), IC28.12 (A3), IC29.12 (A3), IC30.12 (A3), IC31.12 (A3), IC32.12 (A3), IC33.12 (A3), IC34.12 (A3), IC35.12 (A3), IC36.12 (A3), IC37.12 (A3), IC38.12 (A3), IC39.12 (A3), IC40.12 (A3), R24.P$2
RA4: IC13.4 (1Y), IC20.7 (1Y), R25.P$1
RA4F: IC25.11 (A4), IC26.11 (A4), IC27.11 (A4), IC28.11 (A4), IC29.11 (A4), IC30.11 (A4), IC31.11 (A4), IC32.11 (A4), IC33.11 (A4), IC34.11 (A4), IC35.11 (A4), IC36.11 (A4), IC37.11 (A4), IC38.11 (A4), IC39.11 (A4), IC40.11 (A4), R25.P$2
RA5: IC13.7 (2Y), IC20.9 (2Y), R26.P$1
RA5F: IC25.10 (A5), IC26.10 (A5), IC27.10 (A5), IC28.10 (A5), IC29.10 (A5), IC30.10 (A5), IC31.10 (A5), IC32.10 (A5), IC33.10 (A5), IC34.10 (A5), IC35.10 (A5), IC36.10 (A5), IC37.10 (A5), IC38.10 (A5), IC39.10 (A5), IC40.10 (A5), R26.P$2
RA6: IC13.12 (4Y), IC21.7 (1Y), R27.P$1
RA6F: IC25.13 (A6), IC26.13 (A6), IC27.13 (A6), IC28.13 (A6), IC29.13 (A6), IC30.13 (A6), IC31.13 (A6), IC32.13 (A6), IC33.13 (A6), IC34.13 (A6), IC35.13 (A6), IC36.13 (A6), IC37.13 (A6), IC38.13 (A6), IC39.13 (A6), IC40.13 (A6), R27.P$2
RA7: IC13.9 (3Y), IC21.9 (2Y), R28.P$1
RA7F: IC25.9 (A7), IC26.9 (A7), IC27.9 (A7), IC28.9 (A7), IC29.9 (A7), IC30.9 (A7), IC31.9 (A7), IC32.9 (A7), IC33.9 (A7), IC34.9 (A7), IC35.9 (A7), IC36.9 (A7), IC37.9 (A7), IC38.9 (A7), IC39.9 (A7), IC40.9 (A7), R28.P$2
RA8: IC14.7 (1Y), R31.P$1
RA8F: IC25.1 (A8), IC26.1 (A8), IC27.1 (A8), IC28.1 (A8), IC29.1 (A8), IC30.1 (A8), IC31.1 (A8), IC32.1 (A8), IC33.1 (A8), IC34.1 (A8), IC35.1 (A8), IC36.1 (A8), IC37.1 (A8), IC38.1 (A8), IC39.1 (A8), IC40.1 (A8), R31.P$2
RAM: IC25.3 (!WE), IC26.3 (!WE), IC27.3 (!WE), IC28.3 (!WE), IC29.3 (!WE), IC30.3 (!WE), IC31.3 (!WE), IC32.3 (!WE), IC33.3 (!WE), IC34.3 (!WE), IC35.3 (!WE), IC36.3 (!WE), IC37.3 (!WE), IC38.3 (!WE), IC39.3 (!WE), IC40.3 (!WE), R79.P$2
RAMR/!W: IC7.13 (O1), R79.P$1
RD0: IC48.17 (A4), R2.P$1
RD1: IC48.15 (A3), R14.P$1
RD2: IC48.13 (A2), R15.P$1
RD3: IC48.11 (A1), R16.P$1
RD4: IC48.8 (A4), R17.P$1
RD5: IC48.6 (A3), R18.P$1
RD6: IC48.4 (A2), R19.P$1
RD7: IC48.2 (A1), R20.P$1
RED: CN8.1, CN13.1
RESLIN: IC3.18 (O6), IC16.12 (CLR), IC17.2 (CLR), IC17.12 (CLR)
RESYNB: IC3.19 (O7), IC16.2 (CLR), IC16.13 (A)
ROM_CE: IC41.22 (!CE), IC42.22 (!CE), IC49.13 (O)
RQ0: IC6.2 (I0), IC9.2 (A1), IC24.2 (A), IC25.14 (DOUT)
RQ1: IC6.3 (I1), IC9.4 (A2), IC24.3 (B), IC29.14 (DOUT)
RQ2: IC6.4 (I2), IC9.6 (A3), IC24.4 (C), IC33.14 (DOUT)
RQ3: IC6.5 (I3), IC9.8 (A4), IC24.5 (D), IC37.14 (DOUT)
RQ4: IC6.6 (I4), IC9.17 (A4), IC24.10 (E), IC26.14 (DOUT)
RQ5: IC6.7 (I5), IC9.15 (A3), IC24.11 (F), IC30.14 (DOUT)
RQ6: IC9.13 (A2), IC24.12 (G), IC34.14 (DOUT)
RQ7: IC9.11 (A1), IC24.14 (H), IC38.14 (DOUT)
RQ8: IC10.2 (A1), IC23.2 (A), IC27.14 (DOUT), IC50.3 (A)
RQ9: IC10.4 (A2), IC23.3 (B), IC31.14 (DOUT), IC50.4 (B)
RQ10: IC10.6 (A3), IC23.4 (C), IC35.14 (DOUT), IC50.5 (C)
RQ11: IC10.8 (A4), IC23.5 (D), IC39.14 (DOUT), IC50.6 (D)
RQ12: IC10.17 (A4), IC23.10 (E), IC28.14 (DOUT), IC51.3 (A)
RQ13: IC10.15 (A3), IC23.11 (F), IC32.14 (DOUT), IC51.4 (B)
RQ14: IC10.13 (A2), IC23.12 (G), IC36.14 (DOUT), IC51.5 (C)
RQ15: IC10.11 (A1), IC23.14 (H), IC40.14 (DOUT), IC51.6 (D)
RTC.CLK: IC46.11 (PB1), IC47.7 (PB2(SCK/ADC1))
RTC.DATA: IC46.10 (PB0), IC47.6 (PB1(MISO))
RXDA: IC11.13 (RXDA), IC22.P$3 (OUT_A)
RXDB: IC11.27 (RXDB), IC22.P$13 (OUT_B)
S5: IC13.2 (1A), IC13.11 (3A), IC13.14 (4A), IC21.12 (2C2), IC22.P$4 (ENABLE), IC23.9 (CLR), IC24.1 (SER), IC24.9 (CLR), R54.P$2
SER: IC23.1 (SER), IC24.13 (QH)
SND: IC45.11 (I), IC51.15 (RCO)
SND_OUT: C4.P$1, CN6.RING, CN6.TIP, R80.P$2
SND_RES: IC45.9 (I), IC46.17 (PB7)
SPEAKER: CN14.2, R13.P$2
SV0: IC44.12 (C), IC46.2 (PA0)
SV1: IC44.6 (C), IC46.3 (PA1)
SV2: IC44.5 (C), IC46.4 (PA2)
SWITCHED_RED: CN13.2, R89.P$2, R90.P$2, R91.P$2, R92.P$2, R93.P$2
TC: IC2.15 (O3), IC3.6 (I4), IC5.4 (I2), IC6.9 (I7), IC16.1 (A)
TSEN0: IC2.11 (OE/I8), IC7.11 (OE/I8), R56.P$2
TSEN1: IC3.11 (OE/I8), R57.P$2
TSEN2: IC5.11 (OE/I8), IC6.11 (OE/I8)
TXDA: IC11.15 (TXDA), IC15.P$2 (IN_A)
TXDB: IC11.25 (TXDB), IC15.P$7 (IN_D)
VA0: IC3.9 (I7), IC16.3 (QA), IC19.3 (1C3)
VA1: IC3.8 (I6), IC16.4 (QB), IC19.13 (2C3)
VA2: IC3.7 (I5), IC16.5 (QC), IC18.3 (1C3)
VA3: IC3.4 (I2), IC16.6 (QD), IC18.13 (2C3)
VA4: IC16.11 (QA), IC20.3 (1C3)
VA5: IC12.3 (1B), IC16.10 (QB), IC20.13 (2C3)
VA6: IC8.3 (I2), IC12.6 (2B), IC16.9 (QC), IC21.3 (1C3)
VA7: IC8.2 (I1), IC12.13 (4B), IC16.8 (QD), IC17.1 (A), IC21.13 (2C3)
VA8: IC8.1 (I0), IC12.10 (3B), IC17.3 (QA), IC19.4 (1C2)
VA9: IC7.4 (I2), IC13.3 (1B), IC17.4 (QB), IC19.12 (2C2)
VA10: IC7.5 (I3), IC13.6 (2B), IC17.5 (QC), IC18.4 (1C2)
VA11: IC7.6 (I4), IC13.13 (4B), IC17.6 (QD), IC17.13 (A)
VA12: IC7.14 (O2), IC13.10 (3B), IC18.12 (2C2), IC20.4 (1C2)
VA13: IC7.17 (O5), IC12.2 (1A), IC20.12 (2C2)
VC0: IC3.2 (I0), IC8.18 (O6)
VC1: IC3.3 (I1), IC8.19 (O7)
VGA-HSYNC: CN8.13, R83.P$2
VGA-VSYNC: CN8.14, R82.P$2
VID/U: IC2.4 (I2), IC3.15 (O3), IC14.2 (B), IC18.2 (B), IC19.2 (B), IC20.2 (B), IC21.2 (B)

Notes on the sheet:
Note: This design is based on the Pico VGA Scan Converter by GuruThree: https://github.com/guruthree/mac-se-video-converter VGA Interface is based off the RP2040 reference design: https://datasheets.raspberrypi.com/rp2040/hardware-design-with-rp2040.pdf
DosFox
N/A
The OSHintosh, an Open Source SBC Macintosh
Onboard Power LED
Engineers Note: When testing, assemble and test POR first. It has been checked and appears good, but it's a little bit sketchy
5.1V Zener
128 to 512 Address Decoder (Dr. Dobbs)
Ferrite Voltage Rails
-5V Regulator
Power On Reset and Switch
15.6672mhz Oscillator
Volume Control, Audio Amplifier and Headphone Connector
Engineers Note: Design identical to Sony SND THT design, which has been proven to work.
System ROMs and Address Logic
Engineers Note: The 74ls02 is also used as the decode logic for the onboard Rominator See Schwim Github for how this works. I still hate it.
Keyboard Interface
ATTINY85 RTC
Mouse Interface
Schwim Buffers, Resistor Array and Address Decode Logic
Engineers Note: Built in Rominator, to allow the system to boot from ROM.
Zilog SCC Serial Controller
MOS 6522 VIA I/O Controller
RS422 Ports and Line Transcievers
MC68000 CPU and Interrupt Switch
512K System DRAM (41256 ICs)
System PALS: TSM, TSG, LAG, BMU0, BMU1, ASG
Engineers Note: All of the PALs (BMU1 included) are intended to be replaced with GAL16V8s
Engineers Note: This design was taken from the Dr. Dobbs article "how to fatten your Mac": https://dserver.macgui.com/Dr%20Dobbs%20Fatten%20Your%20Mac%201985.pdf
DRAM Data Bus Buffers
Assorted Inverters
Engineers Note: Assorted inverters, using a single 74ls04 hex inverter. Note the sixth inverter is used for the Rominator Output Enable
Address Lines and TSEN signals
Current Limiting Resistors
Pull Up/Down Resistors
RAS, CAS, RAM Address and System Clocks
Sound Counter ICs
Video Output Shift Registers
DRAM Video Address/Audio Address Multiplexers
DRAM Video Address/System Address Multiplexers

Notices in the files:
Eagle Files/OSHintosh.brd:
Released Under CERN-OHL-P
parts and their libraries:
SparkFun-Retired: Licensing: Creative Commons ShareAlike 4.0 International - https://creativecommons.org/licenses/by-sa/4.0
